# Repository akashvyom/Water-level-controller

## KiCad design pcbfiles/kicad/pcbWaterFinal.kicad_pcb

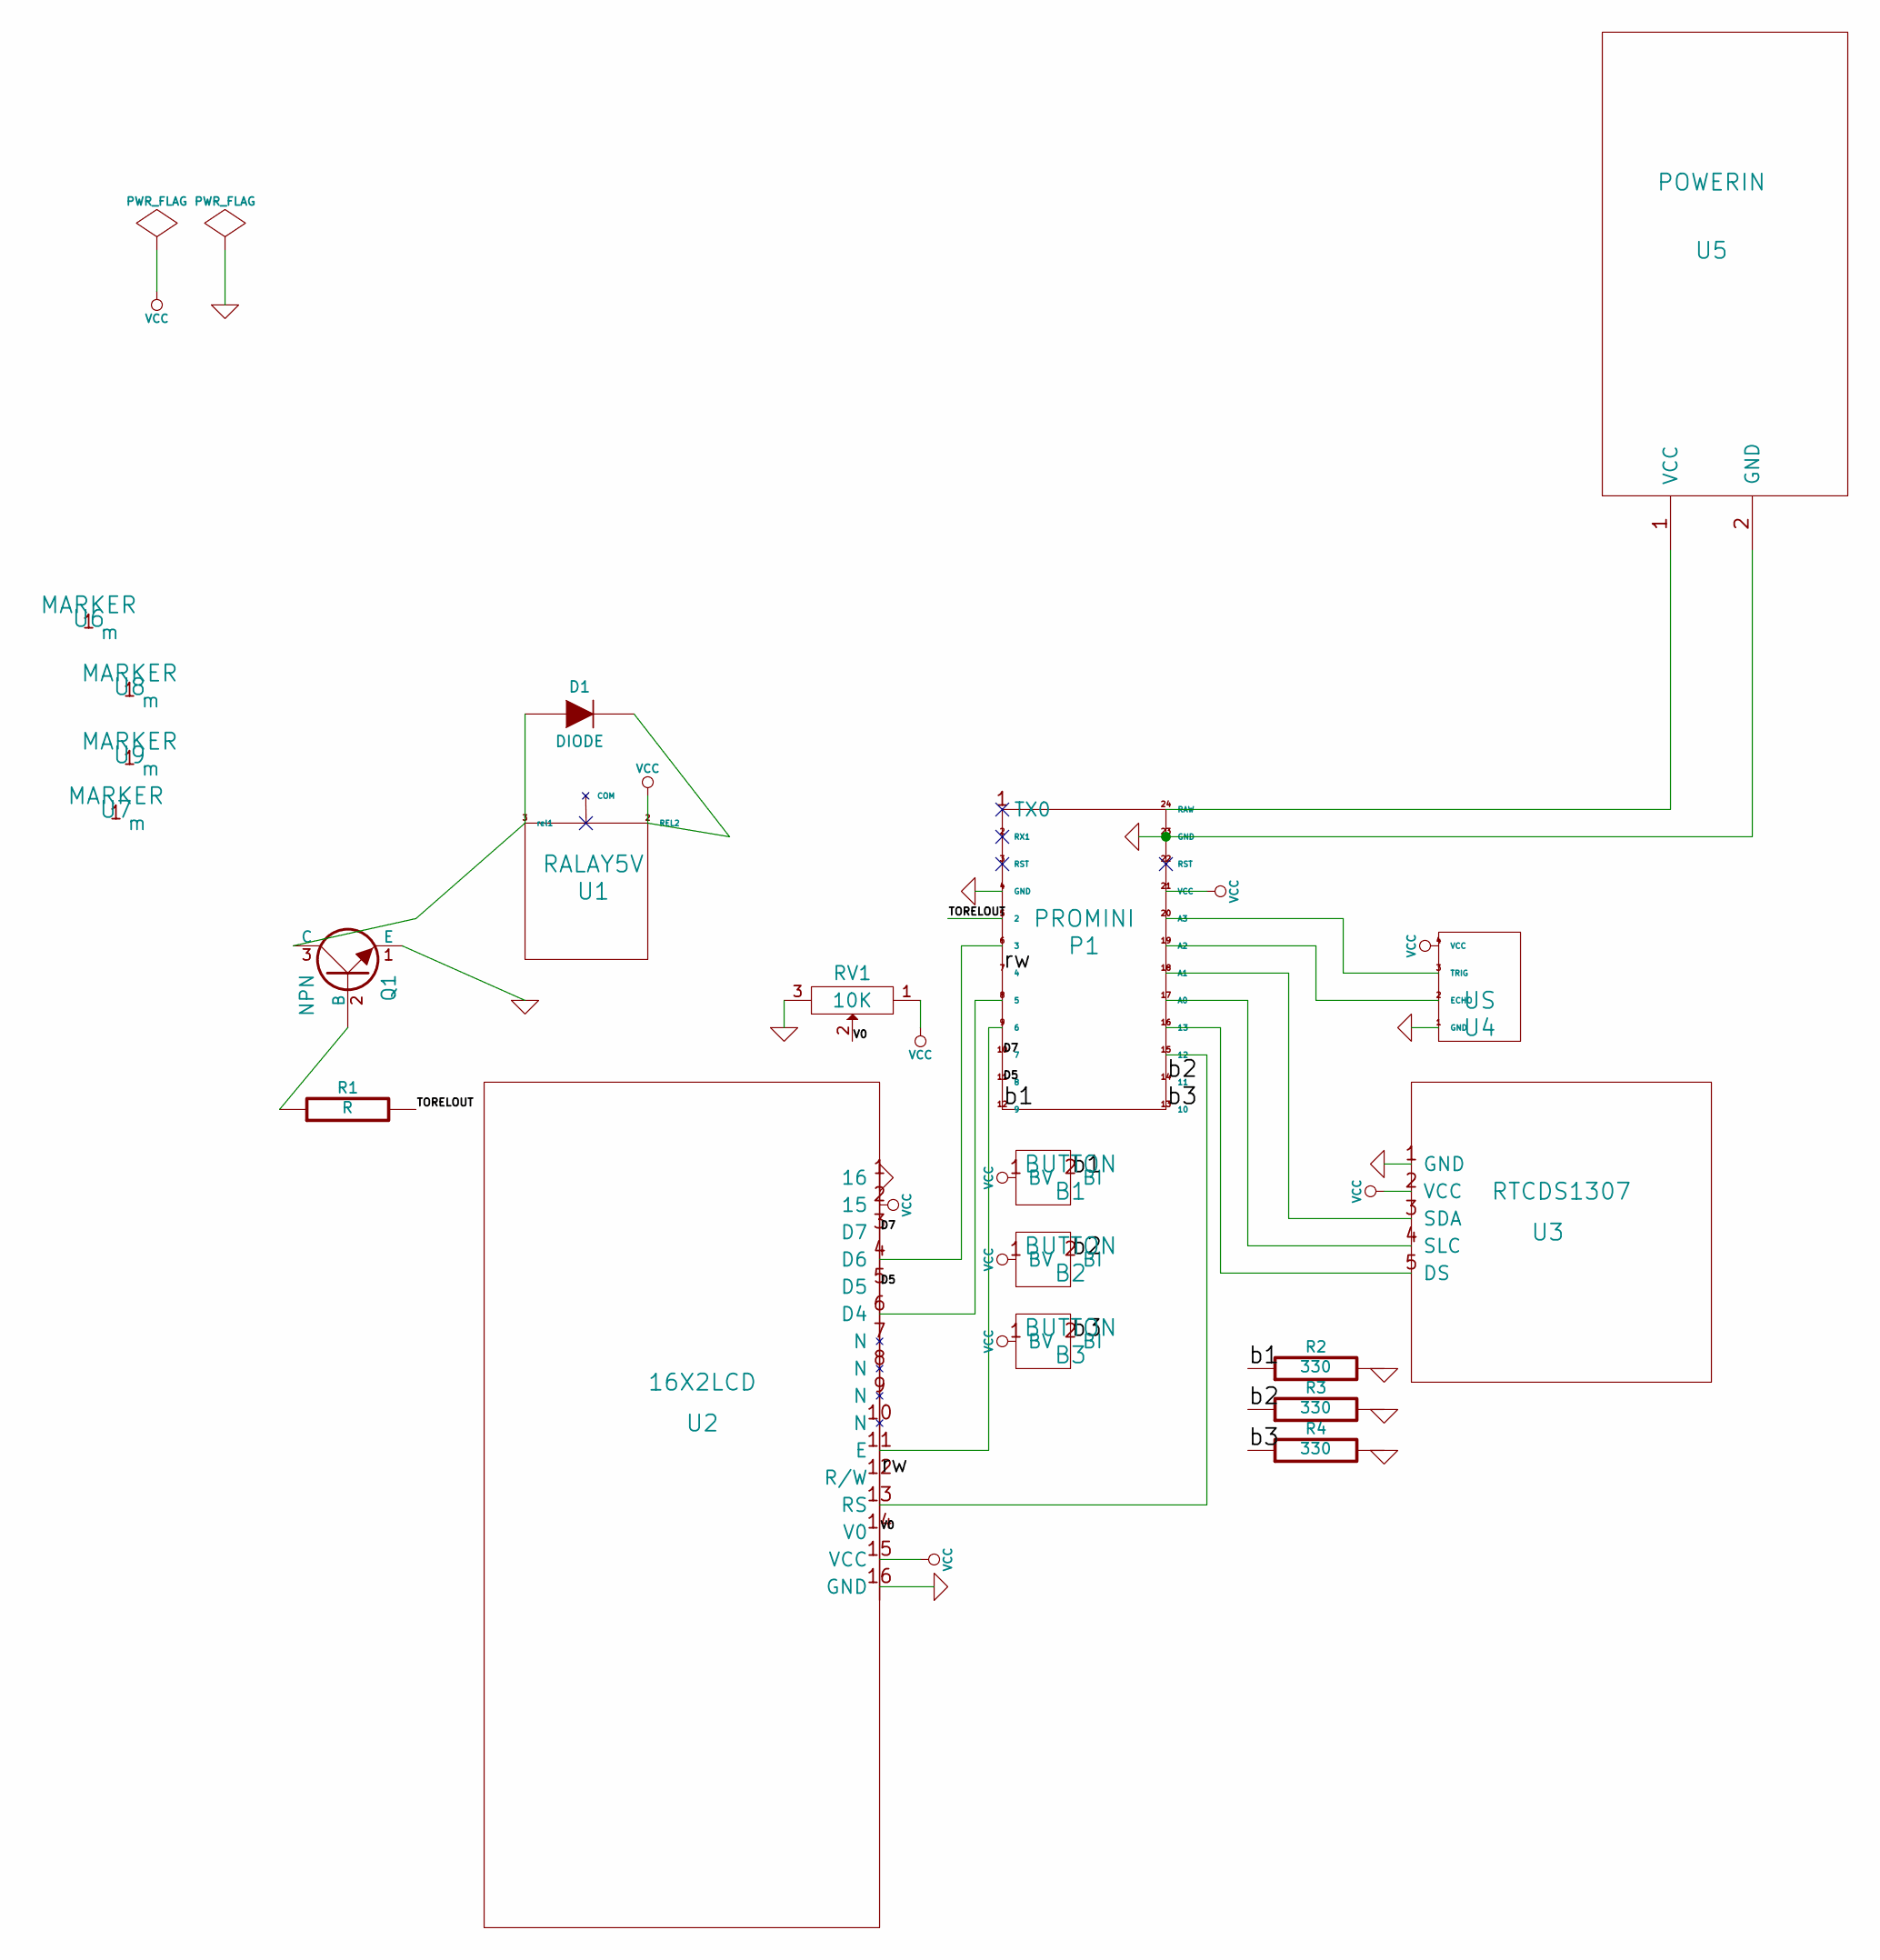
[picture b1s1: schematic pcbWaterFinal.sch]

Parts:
B1, B2, B3: BUTTON
D1: DIODE
P1: PROMINI
Q1: NPN
R1: R
R2, R3, R4: 330
RV1: 10K
U1: RALAY5V
U2: 16X2LCD
U3: RTCDS1307
U4: US
U5: POWERIN
U6, U7, U8, U9: MARKER

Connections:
/D5: P1.11 (8), U2.5 (D5)
/D7: P1.10 (7), U2.3 (D7)
/TORELOUT: P1.5 (2), R1.2
/V0: RV1.2, U2.14 (V0)
/b1: B1.2 (BI), P1.12 (9), R2.1
/b2: B2.2 (BI), P1.14 (11), R3.1
/b3: B3.2 (BI), P1.13 (10), R4.1
/rw: P1.7 (4), U2.12 (R/W)
GND: P1.4 (GND), P1.23 (GND), Q1.1 (E), R2.2, R3.2, R4.2, RV1.3, U2.1 (16), U2.16 (GND), U3.1 (GND), U4.1 (GND), U5.2 (GND)
unnamed: P1.16 (13), U3.5 (DS)
unnamed: P1.19 (A2), U4.2 (ECHO)
unnamed: P1.18 (A1), U3.3 (SDA)
unnamed: P1.17 (A0), U3.4 (SLC)
unnamed: Q1.2 (B), R1.1
unnamed: D1.1 (A), Q1.3 (C), U1.3 (rel1)
unnamed: P1.6 (3), U2.4 (D6)
unnamed: P1.24 (RAW), U5.1 (VCC)
unnamed: P1.20 (A3), U4.3 (TRIG), U4.~ (TRIG)
unnamed: P1.9 (6), U2.11 (E)
unnamed: P1.8 (5), U2.6 (D4)
unnamed: P1.15 (12), U2.13 (RS)
VCC: B1.1 (BV), B2.1 (BV), B3.1 (BV), D1.2 (K), P1.21 (VCC), RV1.1, U1.2 (REL2), U2.2 (15), U2.15 (VCC), U3.2 (VCC), U4.4 (VCC)

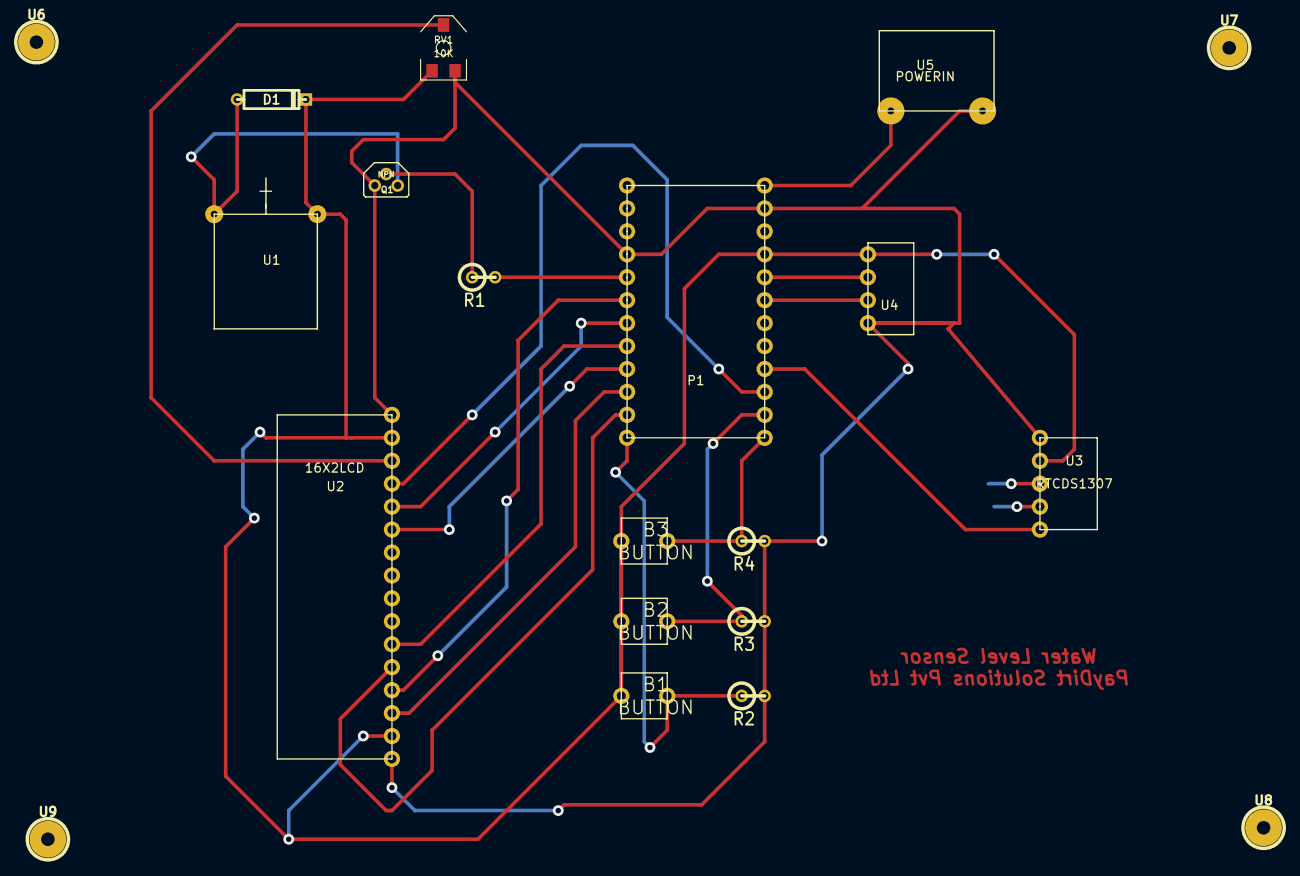
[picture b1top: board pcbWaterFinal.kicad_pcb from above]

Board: 2 copper layers, 20 parts (0 on the bottom side), 22 nets.

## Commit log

2015-01-22 Basic prototype complete
